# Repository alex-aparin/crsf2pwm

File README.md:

# crsf2pwm

CRSF-to-PWM converter for an RC car: receives CRSF from an ExpressLRS or
Crossfire receiver over UART and outputs two servo PWM signals, one for the
steering servo and one for the motor ESC. Plain synthesisable
SystemVerilog, one clock, no vendor primitives. The current target is a
Cyclone IV E development board; a MAX II EPM240 revision exists but the
design is a few logic cells too big for it.

## Layout

```
rtl/          synthesizable code, the only thing that goes into Quartus
tb/           testbenches for Icarus Verilog, one per module plus tb_top
tb/lib/       helpers shared by the testbenches (CRC, frame building)
tb/model/     Python reference model and the test vector generator
tb/vectors/   generated vectors, committed, `make vectors` regenerates them
sim/          Makefile for running simulations, waveforms land here
quartus/      Quartus project: .qpf, one .qsf per revision, .sdc, the clock probe
tools/        build, JTAG check, program, udev rule for the USB Blaster
hw/           KiCad board project
docs/         notes: design, CRSF protocol, servo PWM, pinout, board bring-up
```

## Design

```
rx -> 2 FF sync -> uart_rx -> crsf_parser -> steer_val ----------> pwm_chan -> steer
                                          -> thr_val -> failsafe mux -> pwm_chan -> throttle
                                          -> frame_valid -> link watchdog
                              pwm_timebase -> tick, start, head -> both channels, watchdog
```

`docs/design.md` has the module contracts, the timing, the failsafe policy,
the LE budget and the reasoning behind the choices. `docs/crsf.md` and
`docs/servo_pwm.md` cover the two protocols.

## Tools (Linux)

Simulation and lint from the distribution:

```
sudo apt install iverilog gtkwave make python3 verilator
```

Quartus Prime Lite for synthesis and programming: the small installer from
altera.com (`qinst-lite-linux-<version>.run`, free, needs an account),
components Quartus Prime plus the Cyclone IV device support, and MAX II if
the CPLD revision matters; Questa is not needed. It lands in
`~/altera_lite/<version>/quartus`, which is not on PATH: the scripts in
`tools/` find it by themselves, and `. tools/quartus-env.sh` puts it on
PATH for a shell. The USB Blaster needs `tools/udev-install.sh` once.

Verified with Icarus 11, Verilator 5.052, Quartus Prime Lite 25.1std on
Ubuntu 22.04.

## Simulation

Without make, from the `sim` directory:

```
mkdir build
iverilog -g2012 -Wall -I ../tb/lib -s tb_top -o build/tb_top.vvp ../tb/tb_top.sv ../rtl/*.sv
vvp -N build/tb_top.vvp
gtkwave build/tb_top.vcd
```

With make:

```
cd sim
make                 all testbenches
make tb_top          one testbench
make pwm_out         same as make tb_pwm_out
make waves-tb_top    open waveforms in GTKWave
make lint            Verilator lint, if installed
make vectors         regenerate tb/vectors from the Python model
```

Every testbench is self-checking: it prints `PASS` and exits 0, or prints the
failing checks and exits 1 through `$stop`, so `make` fails and the VS Code
task turns red. A watchdog ends a hung run.

`make waves-tb_top` also loads `sim/tb_top.gtkw` if it exists. Save one from
GTKWave with File > Write Save File to keep the signal layout between runs.

## Continuous integration

`.github/workflows/sim.yml` runs on every push and pull request: all
testbenches in Icarus (`make -C sim -k all`), the Python model self-test with
a check that the committed `tb/vectors/` match the generator, and Verilator
lint of the RTL with `-Wall`. The waveforms of a failed run are attached to
the run as an artifact for a week. The badge above shows the state of `main`.

`.github/workflows/hw.yml` runs on changes under `hw/`: ERC of the schematic
and DRC of the board with kicad-cli 10.0 (through `actions-for-kicad/kicad-actions`),
plus a PDF of the schematic and of the board layers. Reports and PDFs are
attached to the run as the `board` artifact for 30 days. ERC tolerates only
"Pin not connected" on the unused U1 pins, which have no no-connect flags yet.

## VS Code

`.vscode/` has tasks and recommended extensions. Open a testbench or a module
file and press Ctrl+Shift+B: the testbench for that file runs in `sim/`, so
`rtl/pwm_out.sv` and `tb/tb_pwm_out.sv` both run `tb_pwm_out`. Errors from
Icarus appear in the Problems panel. Other tasks under Terminal > Run Task:
waves in GTKWave, run + waves, all testbenches, lint, clean.

The Verilog-HDL extension lints the open file with Icarus on save. The Surfer
extension opens a `.vcd` from `sim/build/` inside VS Code as an alternative
to GTKWave.

## Build and program

The Quartus project `quartus/crsf2pwm.qpf` has three revisions:

| Revision | Target | Output |
|---|---|---|
| `crsf2pwm_c4` | the Saylinx Cyclone IV board, EP4CE6F17C8N | `.sof`, and `.jic` for the flash |
| `clock_probe` | the same board, bring-up helper: oscillator to LEDs and header pins | `.sof` |
| `crsf2pwm` | MAX II EPM240 | `.pof`; 234 of 240 LEs with the area settings in the `.qsf`, see `docs/design.md` |

Everything goes through the scripts in `tools/`, which find Quartus, check
the cable and print the numbers that matter:

```
tools/udev-install.sh            once: let Quartus open the USB Blaster
tools/jtag-check.sh              cable found? board answering?
tools/build.sh [revision]        compile, default crsf2pwm_c4; errors, warnings by code, LEs, slack
tools/program.sh [revision]      into the FPGA over JTAG, gone at power-off
tools/program.sh --flash         into the configuration flash, loads at every power-up
tools/crsf_send.py [options]     play a receiver: CRSF frames from the PC over the board's USB-UART (pyserial)
```

The step-by-step procedure with what to expect at each step, from the
first `jtagconfig` to the car, is `docs/bringup.md`. The GUI works too:
open the `.qpf`, pick the revision under Project > Revisions, Start
Compilation, Programmer.

Current state: the Cyclone IV revision compiles clean in Quartus Prime
Lite 25.1 (273 LEs, Fmax well above 50 MHz) with the pins from
`docs/pinout.md`. Not yet confirmed on the board.

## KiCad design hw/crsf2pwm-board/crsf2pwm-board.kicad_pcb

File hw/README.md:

# Board

KiCad project: `crsf2pwm-board.kicad_pro`, `.kicad_sch`, `.kicad_pcb`.

- `lib/` project symbols, footprints and 3D models, paths via `${KIPRJMOD}`.
- `fab/` gerbers, BOM and position file, committed at the moment of ordering boards.
- Net names as in `docs/pinout.md`.

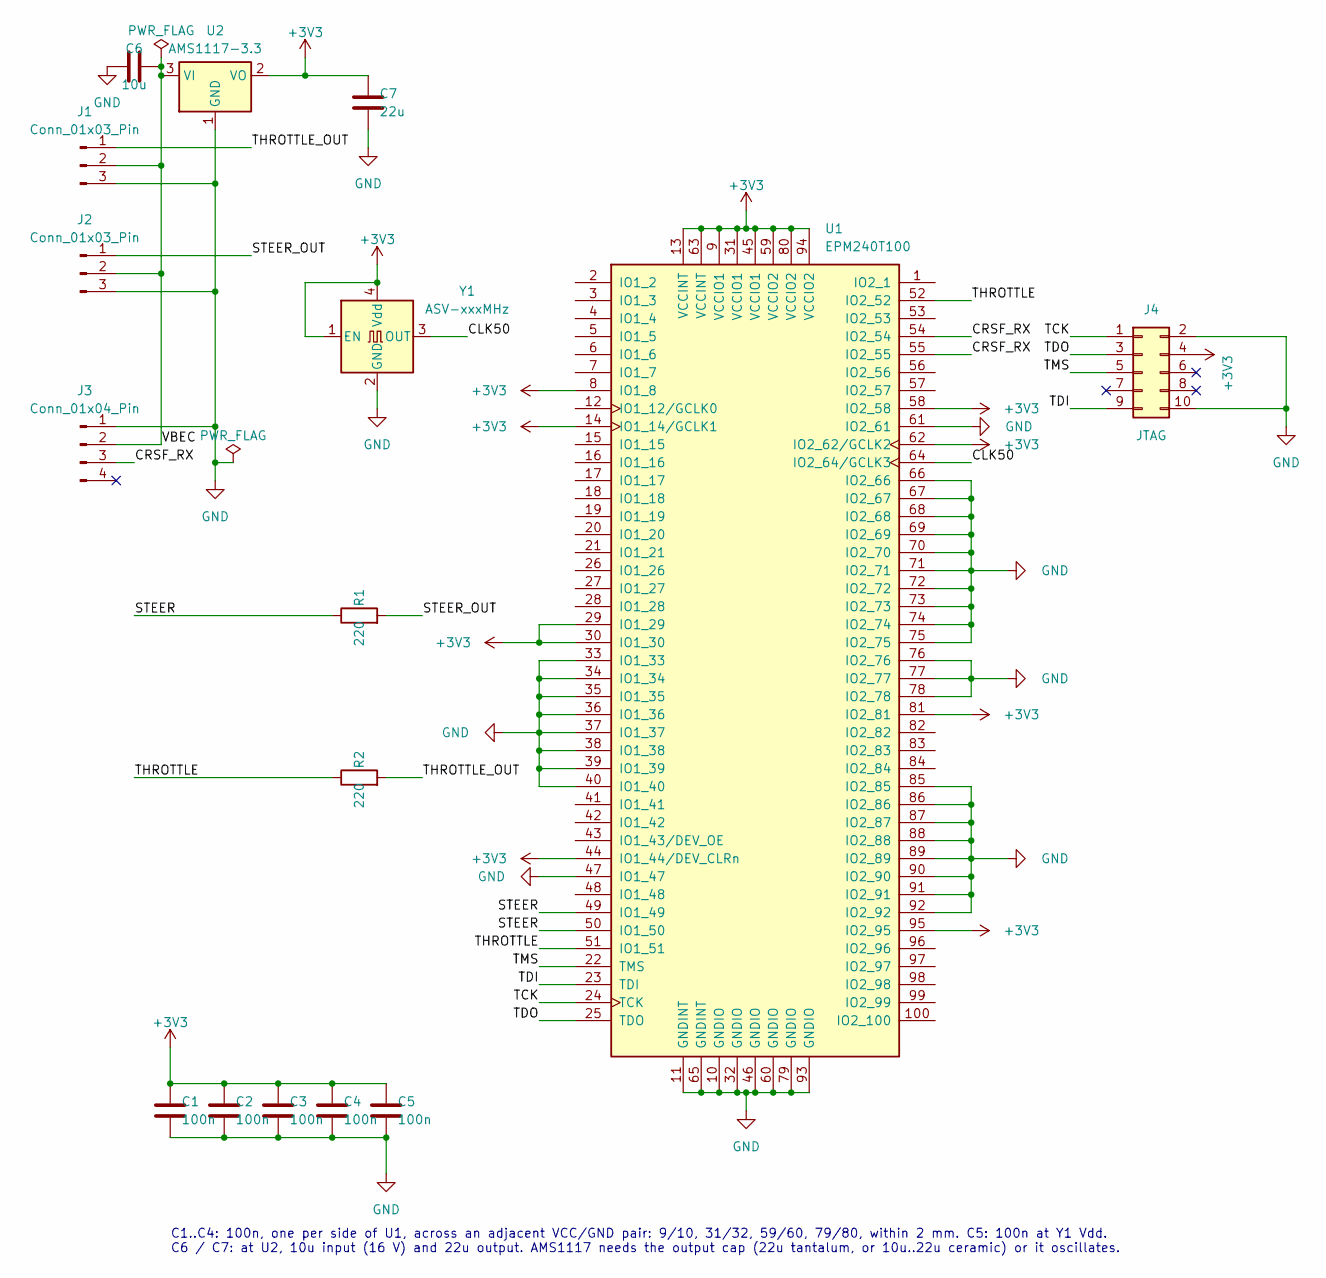
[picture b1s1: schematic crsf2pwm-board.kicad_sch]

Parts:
C1, C2, C3, C4, C5: 100n; C_1206_3216Metric_Pad1.33x1.80mm_HandSolder
C6: 10u; C_1206_3216Metric_Pad1.33x1.80mm_HandSolder
C7: 22u; C_1206_3216Metric_Pad1.33x1.80mm_HandSolder
J1, J2: Conn_01x03_Pin; PinHeader_1x03_P2.54mm_Vertical
J3: Conn_01x04_Pin; PinHeader_1x04_P2.54mm_Vertical
J4: JTAG; IDC-Header_2x05_P2.54mm_Vertical
R1, R2: 220; R_1206_3216Metric_Pad1.30x1.75mm_HandSolder
U1: EPM240T100; LQFP-100_14x14mm_P0.5mm
U2: AMS1117-3.3; SOT-223-3_TabPin2
Y1: ASV-xxxMHz; Oscillator_SMD_Abracon_ASV-4Pin_7.0x5.1mm

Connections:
+3V3: C1.1, C2.1, C3.1, C4.1, C5.1, C7.1, J4.4, U1.8 (IO1_8), U1.9 (VCCIO1), U1.13 (VCCINT), U1.14 (IO1_14/GCLK1), U1.29 (IO1_29), U1.30 (IO1_30), U1.31 (VCCIO1), U1.44 (IO1_44/DEV_CLRn), U1.45 (VCCIO1), U1.58 (IO2_58), U1.59 (VCCIO2), U1.62 (IO2_62/GCLK2), U1.63 (VCCINT), U1.80 (VCCIO2), U1.81 (IO2_81), U1.94 (VCCIO2), U1.95 (IO2_95), U2.2 (VO), Y1.1 (EN), Y1.4 (Vdd)
/CLK50: U1.64 (IO2_64/GCLK3), Y1.3 (OUT)
/CRSF_RX: J3.3, U1.54 (IO2_54), U1.55 (IO2_55)
/STEER: R1.1, U1.49 (IO1_49), U1.50 (IO1_50)
/STEER_OUT: J2.1, R1.2
/TCK: J4.1, U1.24 (TCK)
/TDI: J4.9, U1.23 (TDI)
/TDO: J4.3, U1.25 (TDO)
/THROTTLE: R2.1, U1.51 (IO1_51), U1.52 (IO2_52)
/THROTTLE_OUT: J1.1, R2.2
/TMS: J4.5, U1.22 (TMS)
/VBEC: C6.2, J1.2, J2.2, J3.2, U2.3 (VI)
GND: C1.2, C2.2, C3.2, C4.2, C5.2, C6.1, C7.2, J1.3, J2.3, J3.1, J4.2, J4.10, U1.10 (GNDIO), U1.11 (GNDINT), U1.32 (GNDIO), U1.33 (IO1_33), U1.34 (IO1_34), U1.35 (IO1_35), U1.36 (IO1_36), U1.37 (IO1_37), U1.38 (IO1_38), U1.39 (IO1_39), U1.40 (IO1_40), U1.46 (GNDIO), U1.47 (IO1_47), U1.60 (GNDIO), U1.61 (IO2_61), U1.65 (GNDINT), U1.66 (IO2_66), U1.67 (IO2_67), U1.68 (IO2_68), U1.69 (IO2_69), U1.70 (IO2_70), U1.71 (IO2_71), U1.72 (IO2_72), U1.73 (IO2_73), U1.74 (IO2_74), U1.75 (IO2_75), U1.76 (IO2_76), U1.77 (IO2_77), U1.78 (IO2_78), U1.79 (GNDIO), U1.85 (IO2_85), U1.86 (IO2_86), U1.87 (IO2_87), U1.88 (IO2_88), U1.89 (IO2_89), U1.90 (IO2_90), U1.91 (IO2_91), U1.92 (IO2_92), U1.93 (GNDIO), U2.1 (GND), Y1.2 (GND)

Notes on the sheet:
C1..C4: 100n, one per side of U1, across an adjacent VCC/GND pair: 9/10, 31/32, 59/60, 79/80, within 2 mm. C5: 100n at Y1 Vdd. C6 / C7: at U2, 10u input (16 V) and 22u output. AMS1117 needs the output cap (22u tantalum, or 10u..22u ceramic) or it oscillates.

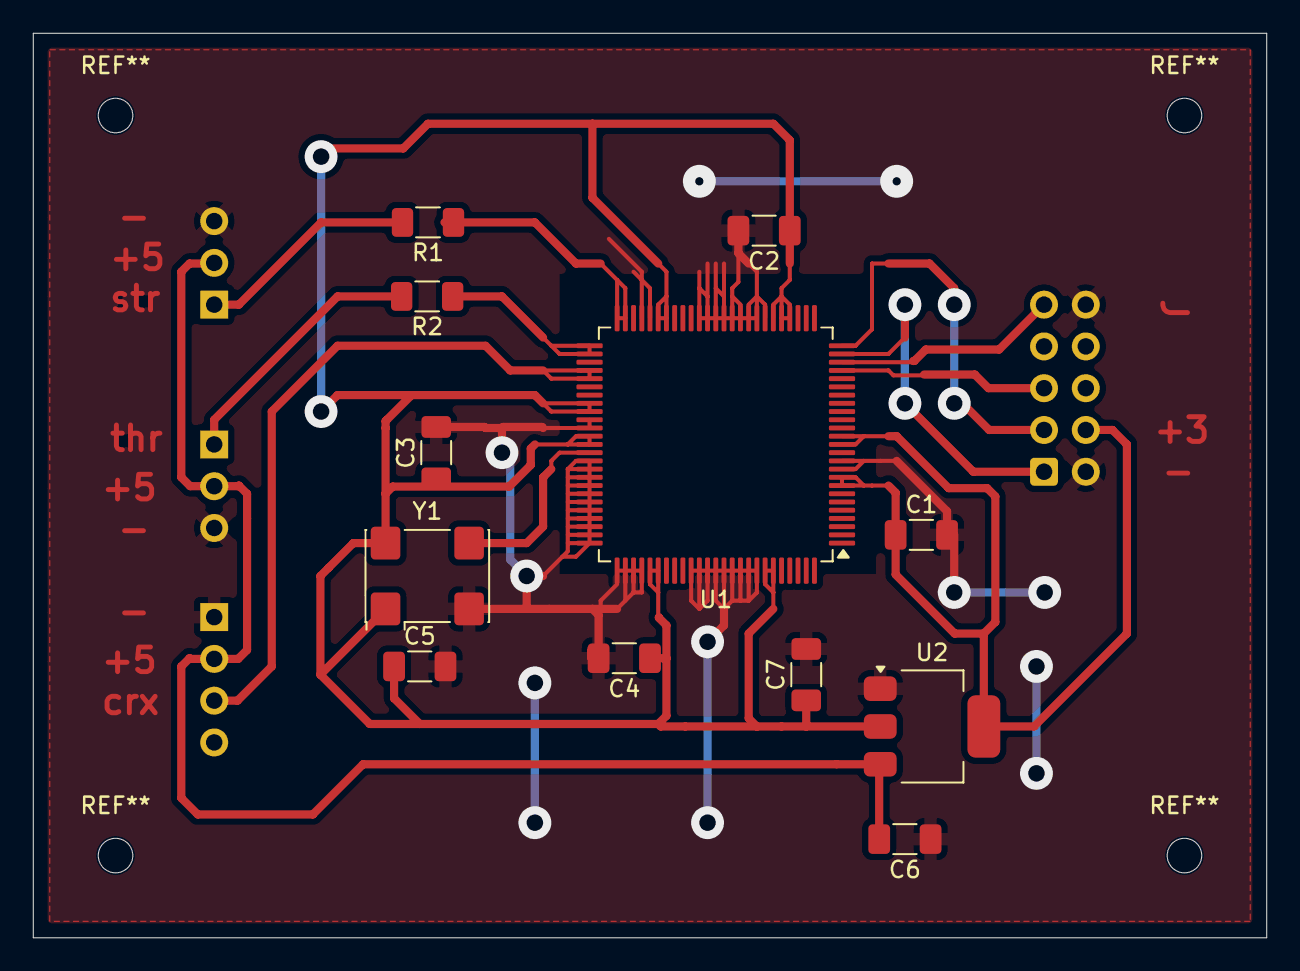
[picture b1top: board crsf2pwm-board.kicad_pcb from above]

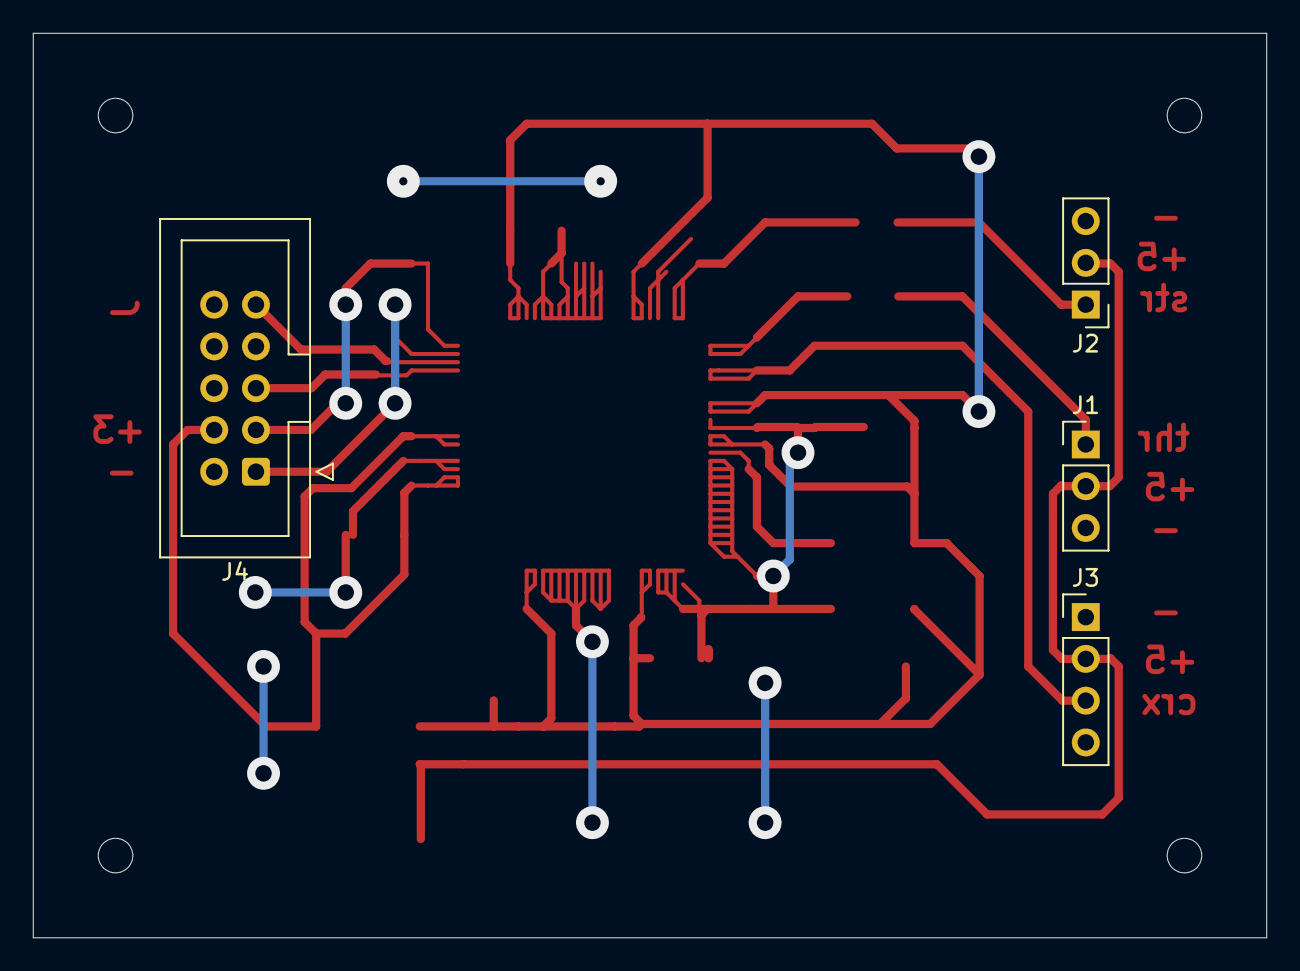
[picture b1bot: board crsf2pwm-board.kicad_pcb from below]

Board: 2 copper layers, 75.0 x 55.0 mm, 16 parts (4 on the bottom side), 13 nets.
